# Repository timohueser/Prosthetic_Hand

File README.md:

# Prosthetic_Hand_V1
## Overview
The aim of this project is to design a 3D printable hand prosthesis. The hand uses 6 cheap geared DC motors that are readily available from Ebay and other places for it's 6 degrees of freedom. Motor control is achieved through a custom made Motor driver PCB that also handles force measurements for each finger. All the 3D models in STEP and STL format are available in this repository, as well as the KiCad design files and schematic of the PCB. The hand is fully self contained and only requires an external power supply and a SPI control signal to be operated. A new version of the prosthetic hand based on this design can be found here: https://github.com/timohueser/Prosthetic_Hand_V2.

## Technical Details
### Fingers
The fingers are fully 3D printable and have 2 joints that move proportional to each other. It was decided to use rigid parts to drive the fingers instead of a string based system. This increases reliability and overall robustness but gives up some of the compliance that a string based system allows. The finger gets driven by a geared DC motor with a lead screw attached to its ouput shaft. A lead screw mechanism has the advantage of not being backdrivable, so the motor does not need to supply the holding torque for the fingers and only needs to be active during movement. With the motor gear ratio choosen the hand achieves reasonable movement speeds while still being able to apply ample force for tasks like picking up everyday objects. Unfortunately the way the lead screw mechanism is implemented in this version of the hand is not very durable, this is mainly due to the low quality of the lead screw and nut and the assymetric way the force gets applied to the lead screw with the current design. Version 2 of the prostehic hand mostly solves this reliability problem. Version 2 also replaces the cheap geared motors used in this version with high quality Maxon Dc motors that can produce significantly more power because of their higher efficiency. Also overall reliability of motor windings and the gearbox are obvious drawbacks of using the cheap motors compared to high quality ones. 

### Thumb
Similar to the other fingers the thumb uses a lead screw machanism to be positioned. In contrast to the other fingers the thumb has two degrees of freedom controlled by two seperate motors. One motor is placed inside the thumb itself and is responsible for flexion and extension of the thumb while the other sits inside the palm of the hand and controls abduction and adduction. This allows a variety of disserent gripping patterns, that the hand can switch bewtween quickly and without needing to be manually adjusted with the other hand. Having one of the motors inside the thumb is necessary to fit the realtively big motors choosen for this project inside the hand, but leads to a less than optimal weight distribution.
Furthermore the exact geometry, like for example the axis of rotation for abduction, still requires a lot of finetuning since the current geometry causes very unnatural positioning of the thumb for certain gripping patterns. Adding compliance to the abduction/adduction joint is a aim for version two, that is expected to greatly improve the capability of the hand to addapt do different objects.

### Motor Driver PCB
The motor driver PCB is based on the L293D Quad Half-H Driver to power the 6 DC motors. It needs to be supplied by a 9-12V motor power supply and a 3-5V supply for the logic and current sense circuitry. The motor supply should be able to handle at least 2 Amps of peak current draw. The motor driver ICs are controlled by a simple 74HC595 shift register, this enables very simple control over the hand over a standard SPI protocoll. Unfortunately there is no encoder readout for the motors for reasons of space constraint. This limits the precision the fingers can be positioned at significantly. 
In addition to motor drive capabilities the circuit also has 6 current sensors, consisting of a current sense resistor and a differential amplifier for each motor to monitor the strain on the motors. This can either be used as crude force feedback to the user of the hand or to limit the torque the hand can apply and stop motors from stalling as soon as the grip is closed. It is also useful as a homing feature since as mentioned previously there is no direct position readout for the fingers. 
Despite adding this position readout using motor drivers with better efficiency is is one of the major improvements that need to be made for the motor driver PCB used in version 2 of the prosthetic hand. The L293D drivers are very inneficient compared to more modern motor driver ICs and produce a lot of excess heat that builds up quickly in the tight and isolated environment the PCB is installed in. In addition many modern motor driver ICs have features like thermal cutoffs and motor current monitoring already built in, allowing for a much more compact PCB design.

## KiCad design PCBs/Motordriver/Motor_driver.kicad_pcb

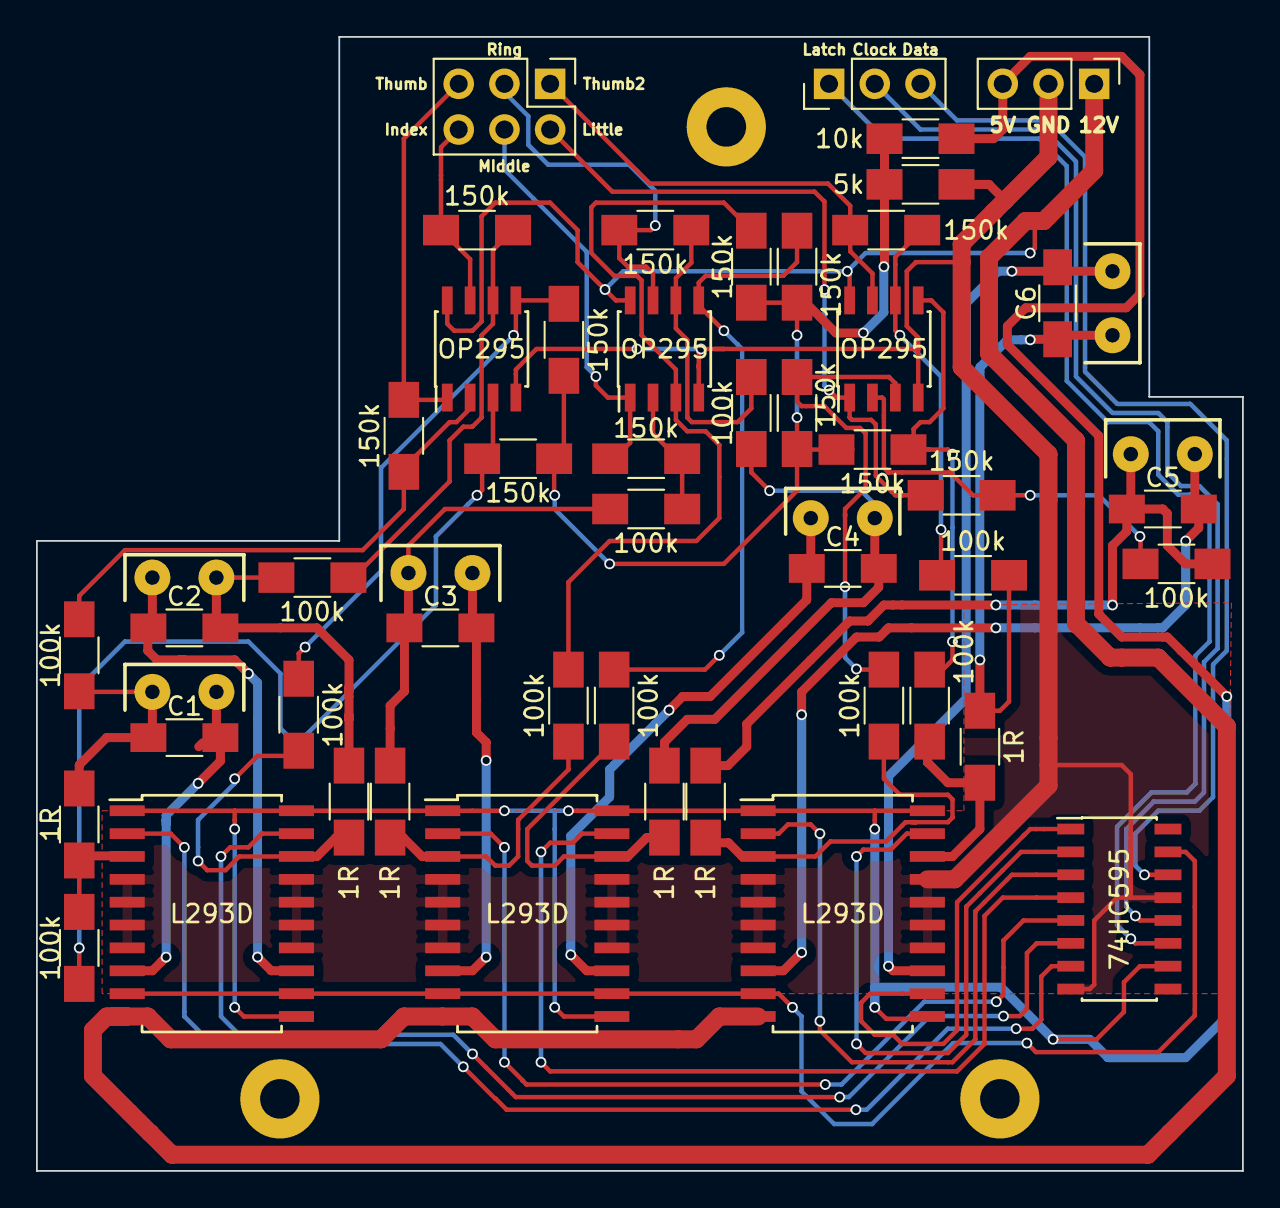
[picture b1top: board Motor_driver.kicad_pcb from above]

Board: 2 copper layers, 67.0 x 63.0 mm, 60 parts (0 on the bottom side), 51 nets.

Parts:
74HC595: 74HC595; SOIC-16_3.9x9.9mm_Pitch1.27mm
C1, C2, C3, C4, C5, C6: C; C_1206_HandSoldering
L293D, L293D#2, L293D#3: L293D; SOIC-20W_7.5x12.8mm_Pitch1.27mm
OP295, OP295#2, OP295#3: TL072; SOIC-8_3.9x4.9mm_Pitch1.27mm
P1, P2, P3, P4, P5, P7, P8, P9, P10, P18, P19: CONN_01X01; SolderWirePad_single_0-8mmDrill
P11, P12: CONN_01X03; Pin_Header_Straight_1x03_Pitch2.54mm
P13: CONN_01X06; Pin_Header_Straight_2x03_Pitch2.54mm
R1, R2, R3, R4, R5, R26: 1R; R_1206_HandSoldering
R6, R7, R12, R13, R14, R17, R18, R19, R24, R25, R27, R30: 150k; R_1206_HandSoldering
R8, R9, R10, R11, R15, R16, R20, R21, R22, R23, R28, R29: 100k; R_1206_HandSoldering
R31: 5k; R_1206_HandSoldering
R32: 10k; R_1206_HandSoldering
wP6: CONN_01X01; SolderWirePad_single_0-8mmDrill

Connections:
+2V5: R12.1, R13.1, R17.1, R24.1, R25.1, R30.1, R31.1, R32.2
+5V: 74HC595.10, L293D.1, L293D.11, L293D.20, L293D#2.1, L293D#2.11, L293D#2.20, L293D#3.1, L293D#3.11, L293D#3.20, P11.3, R32.1
+12V: L293D.10, L293D#2.10, L293D#3.10, OP295.8, OP295#2.8, OP295#3.8, P11.1
Clock: 74HC595.12, P12.2
Common: 74HC595.15, L293D.9, L293D.12, L293D#2.9, L293D#2.12, L293D#3.9
Data: 74HC595.14, P12.3
GND: 74HC595.8, 74HC595.13, L293D.4, L293D.5, L293D.6, L293D.7, L293D.14, L293D.15, L293D.16, L293D.17, L293D#2.4, L293D#2.5, L293D#2.6, L293D#2.7, L293D#2.14, L293D#2.15, L293D#2.16, L293D#2.17, L293D#3.4, L293D#3.5, L293D#3.6, L293D#3.7, L293D#3.14, L293D#3.15, L293D#3.16, L293D#3.17, OP295.4, OP295#2.4, OP295#3.4, P11.2, R31.2
Index: 74HC595.6, L293D.19
IndexSen1: L293D.18, R2.2, R9.2
IndexSen2: C2.1, P1.1, R2.1, R11.2
Latch: 74HC595.11, P12.1
Little: 74HC595.3, L293D#3.2
LittleSen1: L293D#3.3, R5.2, R21.2
LittleSen2: C5.1, P4.1, R5.1, R23.2
Middle: 74HC595.5, L293D#2.2
MiddleSen1: L293D#2.3, R3.2, R15.2
MiddleSen2: C3.1, P2.1, R3.1, R16.2
unnamed: C1.2, L293D.8, wP6.1
unnamed: C2.2, L293D.13, P7.1
unnamed: C3.2, L293D#2.8, P8.1
unnamed: C4.2, L293D#2.13, P9.1
unnamed: C5.2, L293D#3.8, P10.1
unnamed: C6.2, L293D#3.13, P19.1
unnamed: OP295#3.7, P13.1, R27.1
unnamed: OP295#3.1, P13.2, R19.1
unnamed: OP295#2.7, P13.3, R18.1
unnamed: OP295#2.1, P13.4, R14.1
unnamed: OP295.1, P13.5, R6.1
unnamed: OP295.7, P13.6, R7.1
unnamed: OP295.2, R6.2, R10.1
unnamed: OP295.6, R7.2, R11.1
unnamed: OP295.3, R8.1, R12.2
unnamed: OP295.5, R9.1, R13.2
unnamed: OP295#2.2, R14.2, R16.1
unnamed: OP295#2.3, R15.1, R17.2
unnamed: OP295#2.6, R18.2, R22.1
unnamed: OP295#3.2, R19.2, R23.1
unnamed: OP295#2.5, R20.1, R24.2
unnamed: OP295#3.3, R21.1, R25.2
unnamed: OP295#3.6, R27.2, R29.1
unnamed: OP295#3.5, R28.1, R30.2
Ring: 74HC595.4, L293D#2.19
RingSen1: L293D#2.18, R4.2, R20.2
RingSen2: C4.1, P3.1, R4.1, R22.2
Thumb1: 74HC595.7, L293D.2
Thumb2Sen1: L293D#3.18, R26.2, R28.2
Thumb2Sen2: C6.1, P18.1, R26.1, R29.2
Thumb2_a: 74HC595.2, L293D#3.19
Thumb2_b: 74HC595.1, L293D#3.12
ThumbSen1: L293D.3, R1.2, R8.2
ThumbSen2: C1.1, P5.1, R1.1, R10.2
